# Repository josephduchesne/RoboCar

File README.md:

# RoboCar

A robot car that uses the following:

[Hardware](../../wiki/Bill-of-Materials)

Note: When cloning use `git clone --recursive git@github.com:josephduchesne/RoboCar.git` to also checkout the usb_cam submodule.

### Third Party Licenses:

 - 3D_Prints/PanTilt is third party, created by Javier Bernal Mayordomo, Miguel Manzano Olmos, and Arturo Serna León under a [Creative Commons - Attribution - Share Alike](http://creativecommons.org/licenses/by-sa/3.0/) license
 - ROS_Workspace/src/usb_cam is third party and by Robert Bosch LLC. under a [BSD licence](https://github.com/bosch-ros-pkg/usb_cam/blob/develop/LICENSE)
 - ROS_Workspace/src/differential_drive is third party and by Jon Stephan under a [GPLv3 license](http://www.gnu.org/licenses/gpl-3.0.html)

### License

For all files not otherwise noted in Third Party Licenses or by license information contained within the files are licensed under:

The MIT License (MIT)

Copyright (c) 2015 Joseph Duchesne

Permission is hereby granted, free of charge, to any person obtaining a copy
of this software and associated documentation files (the "Software"), to deal
in the Software without restriction, including without limitation the rights
to use, copy, modify, merge, publish, distribute, sublicense, and/or sell
copies of the Software, and to permit persons to whom the Software is
furnished to do so, subject to the following conditions:

The above copyright notice and this permission notice shall be included in
all copies or substantial portions of the Software.

THE SOFTWARE IS PROVIDED "AS IS", WITHOUT WARRANTY OF ANY KIND, EXPRESS OR
IMPLIED, INCLUDING BUT NOT LIMITED TO THE WARRANTIES OF MERCHANTABILITY,
FITNESS FOR A PARTICULAR PURPOSE AND NONINFRINGEMENT. IN NO EVENT SHALL THE
AUTHORS OR COPYRIGHT HOLDERS BE LIABLE FOR ANY CLAIM, DAMAGES OR OTHER
LIABILITY, WHETHER IN AN ACTION OF CONTRACT, TORT OR OTHERWISE, ARISING FROM,
OUT OF OR IN CONNECTION WITH THE SOFTWARE OR THE USE OR OTHER DEALINGS IN
THE SOFTWARE.

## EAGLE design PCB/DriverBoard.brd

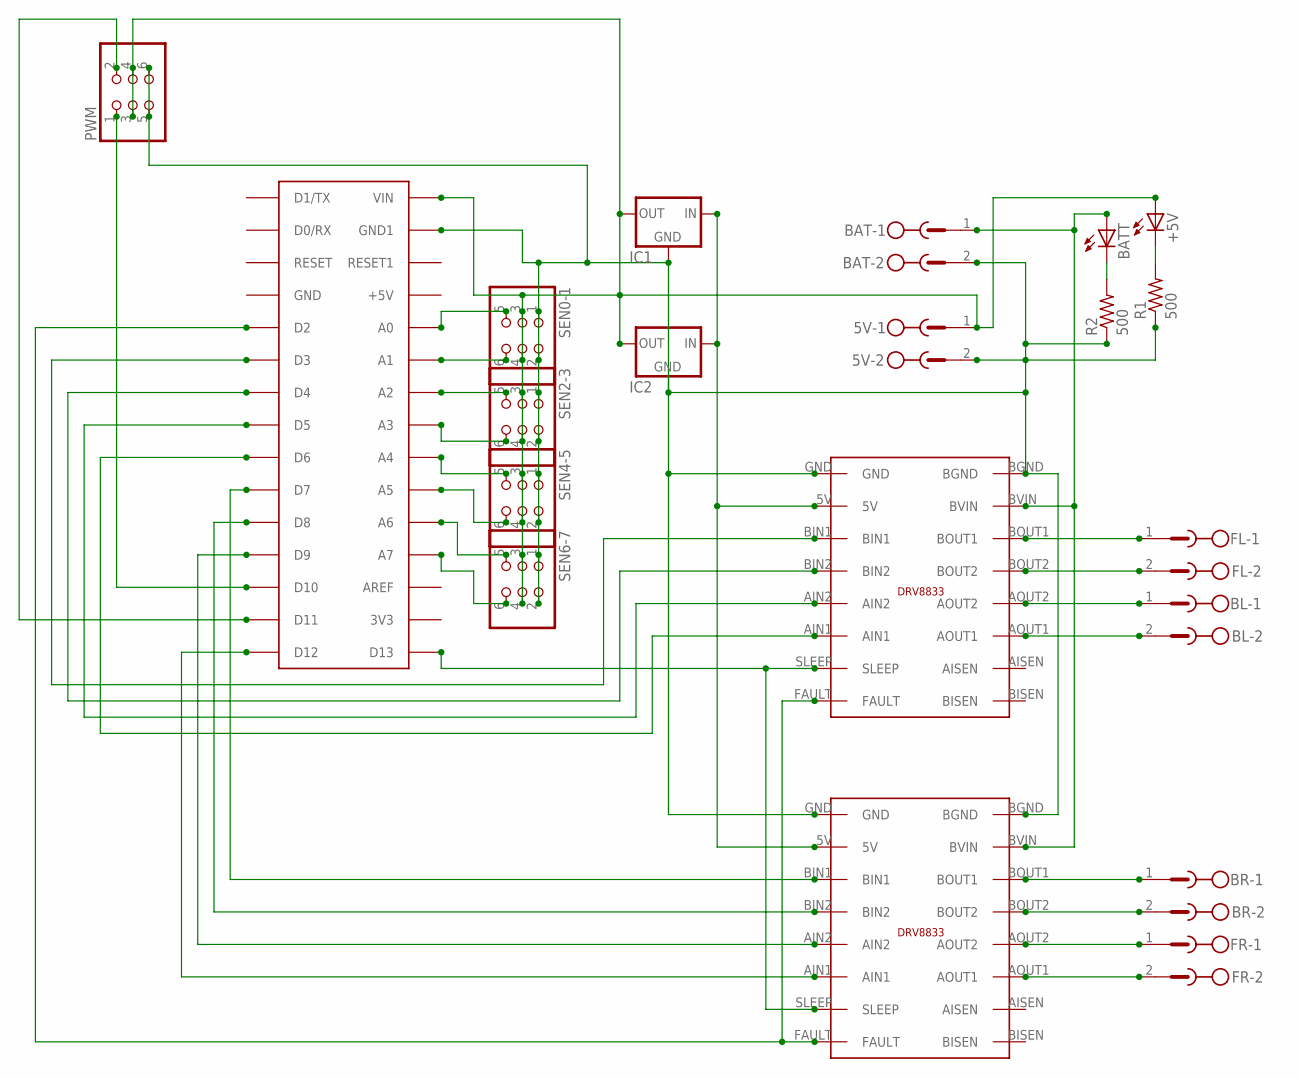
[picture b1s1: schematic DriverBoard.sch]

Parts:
5V: MSTBV2
+5V: LED5MM
BAT: MSTBV2
BATT: LED5MM
BL: MSTBV2
BR: MSTBV2
FL: MSTBV2
FR: MSTBV2
IC1, IC2: 78XXS
PWM: PINHD-2X3; 2X03
R1, R2: 500; 0207/10
SEN0-1, SEN2-3, SEN4-5, SEN6-7: PINHD-2X3; 2X03
U$1: ARDUINONANO; PDIP-32
U$2, U$3: DRV8833

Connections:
unnamed: 5V.2, BAT.2, IC1.GND, IC2.GND, PWM.5, PWM.6, R1.1, R2.1, SEN0-1.1, SEN0-1.2, SEN2-3.1, SEN2-3.2, SEN4-5.1, SEN4-5.2, SEN6-7.1, SEN6-7.2, U$1.GND1, U$2.BGND, U$2.GND, U$3.BGND, U$3.GND
unnamed: FL.1, U$2.BOUT1
unnamed: FL.2, U$2.BOUT2
unnamed: BL.1, U$2.AOUT2
unnamed: BL.2, U$2.AOUT1
unnamed: BR.1, U$3.BOUT1
unnamed: BR.2, U$3.BOUT2
unnamed: FR.1, U$3.AOUT2
unnamed: FR.2, U$3.AOUT1
unnamed: BAT.1, BATT.A, U$2.BVIN, U$3.BVIN
unnamed: U$1.D13, U$2.SLEEP, U$3.SLEEP
unnamed: IC1.IN, IC2.IN, U$2.5V, U$3.5V
unnamed: U$1.D3, U$2.BIN1
unnamed: U$1.D2, U$2.FAULT, U$3.FAULT
unnamed: U$1.D4, U$2.BIN2
unnamed: U$1.D5, U$2.AIN2
unnamed: U$1.D6, U$2.AIN1
unnamed: U$1.D7, U$3.BIN1
unnamed: U$1.D8, U$3.BIN2
unnamed: U$1.D9, U$3.AIN2
unnamed: U$1.D12, U$3.AIN1
unnamed: PWM.1, U$1.D10
unnamed: PWM.2, U$1.D11
unnamed: 5V.1, +5V.A, IC1.OUT, IC2.OUT, PWM.3, PWM.4, SEN0-1.3, SEN0-1.4, SEN2-3.3, SEN2-3.4, SEN4-5.3, SEN4-5.4, SEN6-7.3, SEN6-7.4, U$1.VIN
unnamed: SEN0-1.5, U$1.A0
unnamed: SEN0-1.6, U$1.A1
unnamed: SEN2-3.5, U$1.A2
unnamed: SEN2-3.6, U$1.A3
unnamed: SEN4-5.5, U$1.A4
unnamed: SEN4-5.6, U$1.A5
unnamed: SEN6-7.5, U$1.A6
unnamed: SEN6-7.6, U$1.A7
unnamed: BATT.K (C), R2.2
unnamed: +5V.K (C), R1.2

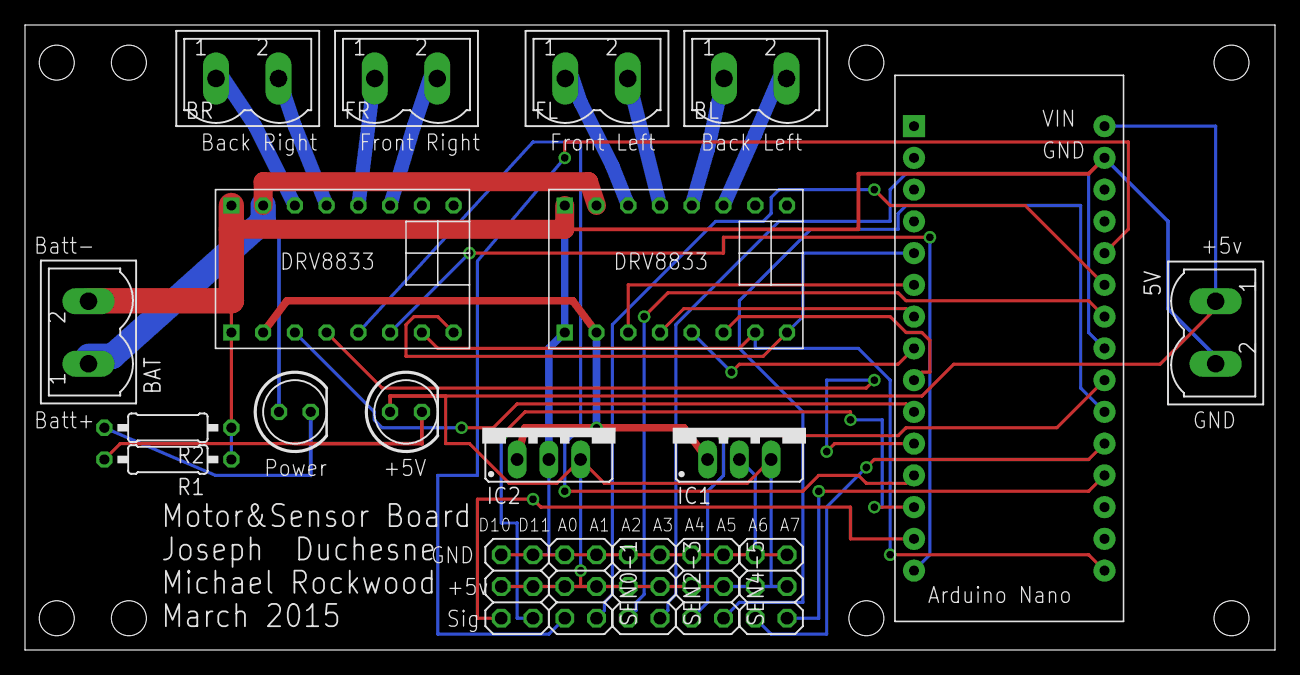
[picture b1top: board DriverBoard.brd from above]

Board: 2 copper layers, 100.0 x 50.0 mm, 20 parts (0 on the bottom side), 34 nets.

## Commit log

2015-03-18 :octocat: Added .gitattributes
2015-03-18 removed unintentionally created dir
2015-03-18 Added readme
2015-03-19 Removed temp file
2015-03-19 Added base for the pan tilt system
2015-03-20 added ROS catkin workspace
2015-03-22 Added pan/tilt base and updated arduino software
    Pan/tilt base 3d model for Futaba S3003 linear servo horn to mount the
    pan/tilt to the bot.
    Also updated arduino software to support pan/tilt
2015-03-23 Servo position estimation
    Added servo position estimation and split motors and servos into
    separate files.
2015-03-23 Expanded on some comments
2015-03-24 added usb_cam module for video streaming
2015-03-24 added a basic temporary prereqs script, and added a camera launcher
2015-03-24 added publisher section of robocar serial node
2015-03-24 Switched startup chime to comment
2015-03-24 added differetial drive
2015-03-24 initial diffferential_drive module
2015-03-24 removed rosbuild manifest
2015-03-24 updated readme to include license
2015-03-24 License update
2015-03-24 removed load_manifest references
2015-03-24 added differential drive config for robocar
2015-03-25 added robocar_drive launch file, vim temp files to the gitignore, and a very basic joystick controller
2015-03-25 serial debugging
2015-03-25 Tweaked servo values
2015-03-26 added CMakeLists.txts
2015-03-26 added controller_environment.sh
2015-03-26 fixed path
2015-03-26 tweaked naming
2015-03-26 fixed joyctl bug
2015-03-26 added debugging tools
2015-03-26 fixed some output issues
2015-03-26 added X11 overrides for pygame and the remote launchs cript
2015-03-26 added camera test launchfile
2015-03-26 Added rangefinder readings
2015-03-26 added environment vars to allow ros to launch x11 windows
2015-03-26 added remote.launch launch everything script
2015-03-27 Fixed the terribly LIDAR reading code
2015-03-27 fixed a few things
2015-03-27 started porting serial node to C++
2015-03-27 implemented input portion of C++ serial_node
2015-03-27 removed debug line
2015-03-27 finished C++ serial node, added camera pit/yaw to py and C++ serial nodes
2015-03-27 increased baud rate
2015-03-27 ported pid_velocity from python to cpp
2015-03-27 added pid test launchfile
2015-03-27 fixed PID subscriptions
2015-03-27 better launch pid params
2015-03-27 fixed a few bugs. Thanks Mike!
2015-03-27 Tweaked arduino code
2015-03-27 renamed serial node, commented out pid debug, reduced queue sizes to 1 mostly, and fixed bug in python serial node
2015-03-27 Slowed down arduino outputs
2015-03-27 moved diff drive in prep for submodule
2015-03-27 added submodule for differential drive
2015-03-27 removed differential drive from this repo since it's now a child repo
2015-03-28 increased PID rate
2015-03-28 added serial node struct and switched all launchfiles to it
2015-03-28 Removed debugging serial output
2015-03-28 modeled robot using urdf for rviz
2015-03-28 added support for moving servos with joyctl and fixed a bug with pitch estimate publishing
2015-03-28 added laser scan to rviz, serial_node_struct, fixed a relative pathing issue, and added dependency on sensor_msgs
2015-03-29 fixed urdf camera orientation, added camera calibration yaml
2015-04-03 Added laser scan sweep mode
    M2/M3 (2nd bit on M command) now sets sweep mode, M0/M1 to disable. This
    performs repeated laser scans back and forth with the yaw servo.
2015-04-03 added mode toggle on joystick button 1
2015-04-03 tweaked rvis config and updated serial node to use new struct format
2015-04-03 added rviz to remote drive launchfile and made serial port a rosparam
2015-04-03 fixed struct size bug
2015-04-04 handle laser scan properly
2015-04-04 tweaked rviz, updated URDF fixed laser scan base
2015-04-04 Tweaked robocar firmware
2015-04-15 Tweaked comment
